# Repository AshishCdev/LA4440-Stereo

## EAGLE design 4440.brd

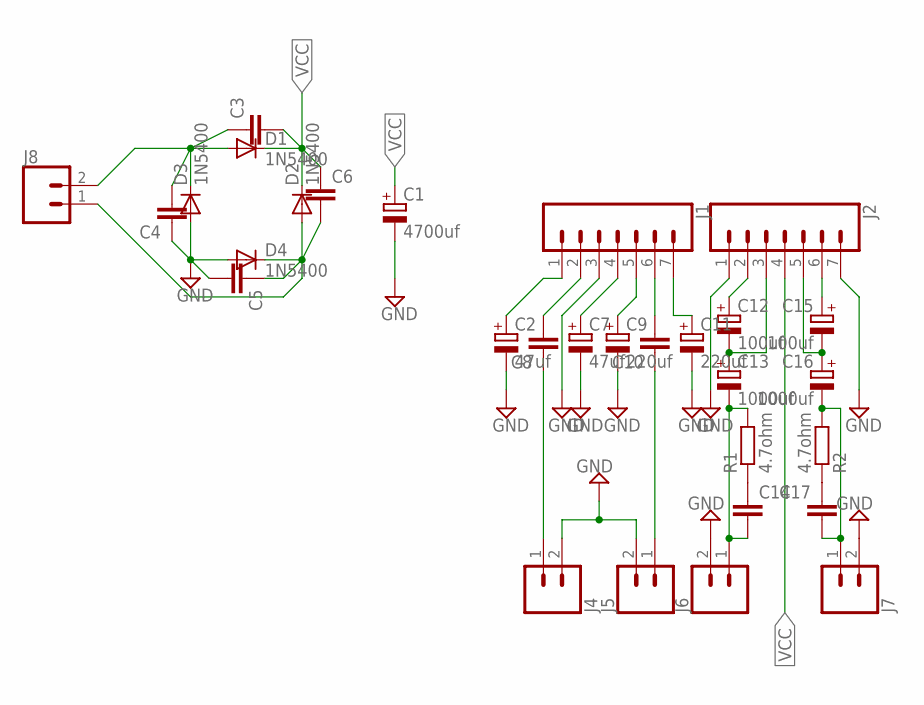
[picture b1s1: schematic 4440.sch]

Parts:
C1: 4700uf; E7,5-16
C2, C7: 47uf; E3,5-8
C3, C4, C5, C6, C8, C10, C14, C17: C-EU050-055X075; C050-055X075
C9, C11: 220uf; E3,5-8
C12, C15: 100uf; E3,5-8
C13, C16: 1000uf; E7,5-16
D1, D2, D3, D4: 1N5400; DO201-15
J1, J2: CONN_07LONGPADS; 1X07_LONGPADS
J4, J5, J6, J7, J8: CONN_023.5MM-NO_SILK; SCREWTERMINAL-3.5MM-2-NS
R1, R2: 4.7ohm; 0207/12

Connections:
GND: C1.-, C2.-, C4.1, C5.2, C7.-, C9.-, C11.-, D3.A, D4.A, J1.3, J2.1, J2.7, J4.2, J5.2, J6.2, J7.2
unnamed: C2.+, J1.1
unnamed: C5.1, C6.2, D2.A, D4.C, J8.1
unnamed: C8.2, J1.2
unnamed: C3.1, C4.2, D1.A, D3.C, J8.2
unnamed: C7.+, J1.4
unnamed: C9.+, J1.5
unnamed: C8.1, J4.1
unnamed: C10.1, J5.1
unnamed: C10.2, J1.6
unnamed: C11.+, J1.7
unnamed: C13.-, C14.2, J6.1, R1.2
unnamed: C12.+, J2.2
unnamed: C12.-, C13.+, J2.3
unnamed: C15.+, J2.6
unnamed: C14.1, R1.1
unnamed: C15.-, C16.+, J2.5
unnamed: C17.1, R2.1
unnamed: C16.-, C17.2, J7.1, R2.2
VCC: C1.+, C3.2, C6.1, D1.C, D2.C, J2.4

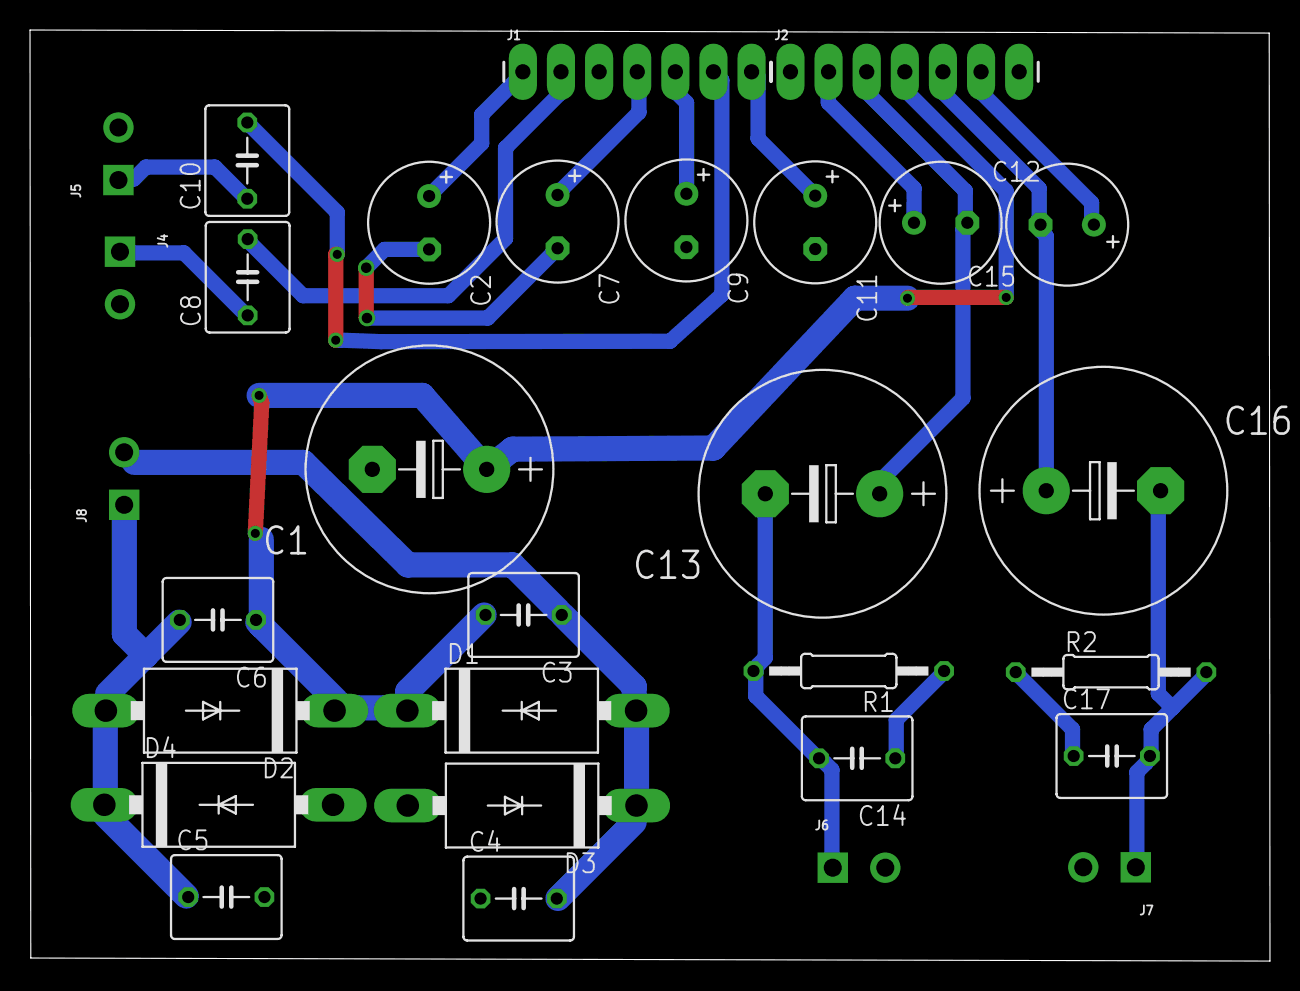
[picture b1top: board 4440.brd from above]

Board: 2 copper layers, 82.6 x 62.0 mm, 30 parts (0 on the bottom side), 20 nets.

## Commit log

2017-05-22 Started project for transfering to the other system
2017-05-22 Completed the layout
2017-05-23 corrected the packages for capacitor
2017-05-23 Completed the project with PCB layout
2017-05-24 Fixed the last missing ground connection

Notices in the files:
parts and their libraries:
SparkFun-Connectors: Licensing: Creative Commons ShareAlike 4.0 International - https://creativecommons.org/licenses/by-sa/4.0
